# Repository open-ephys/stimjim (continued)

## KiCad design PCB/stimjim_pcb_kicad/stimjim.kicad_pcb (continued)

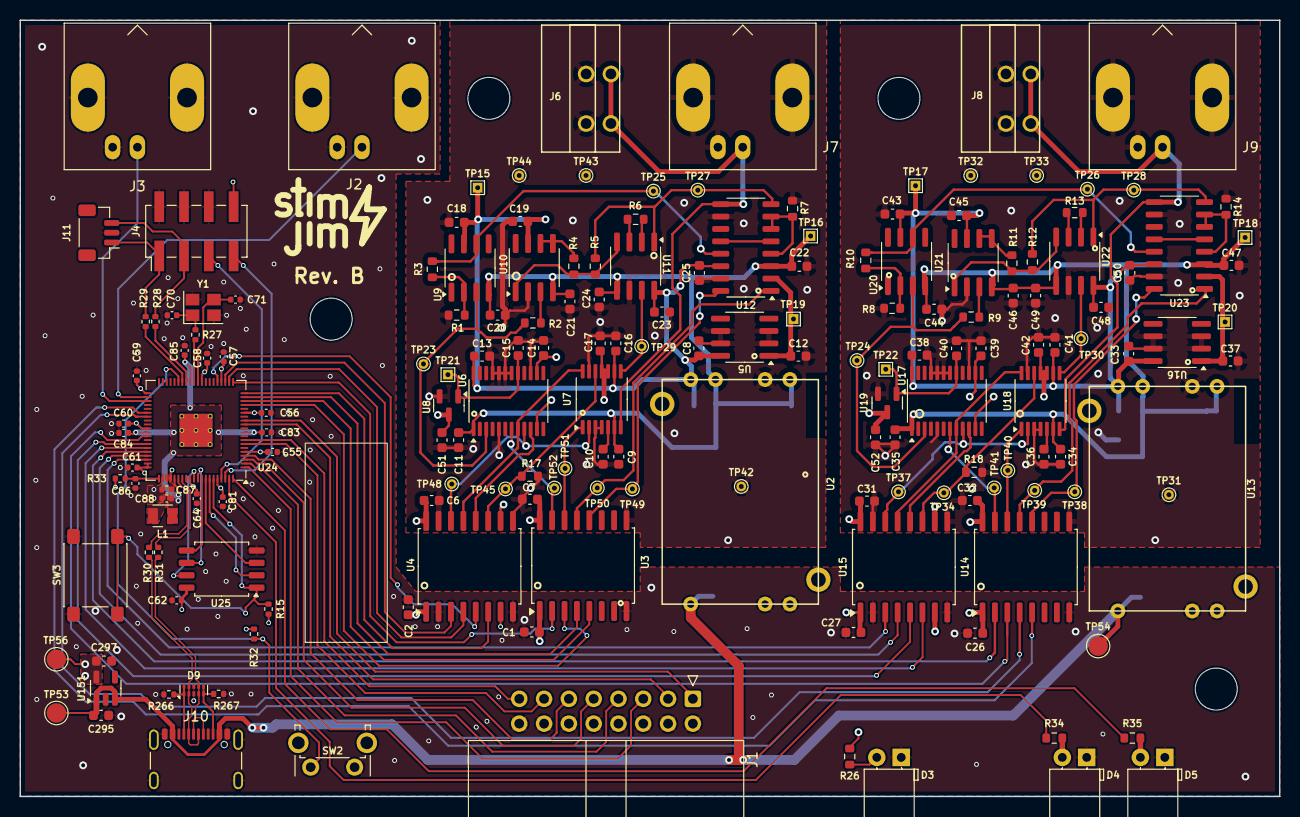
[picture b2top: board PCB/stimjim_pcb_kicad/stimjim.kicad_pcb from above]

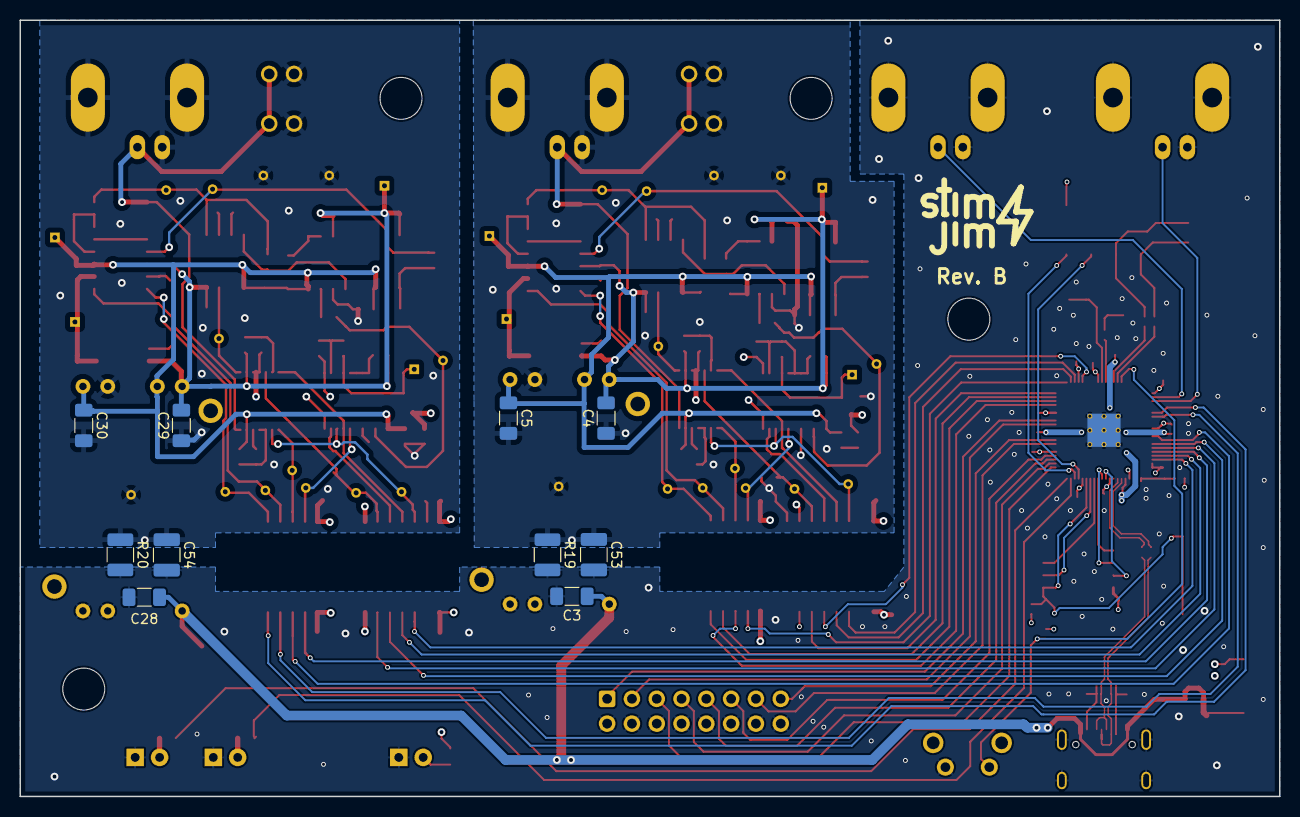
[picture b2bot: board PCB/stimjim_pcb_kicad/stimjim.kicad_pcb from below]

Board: 4 copper layers, 129.0 x 79.5 mm, 190 parts (10 on the bottom side), 113 nets.

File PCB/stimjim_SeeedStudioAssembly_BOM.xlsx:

Designator | MPN | Quantity | Link |  | Package | Designation | Unit cost | Total cost | Assembly notes
C26,C27,C31,C32,C34,C35,C38,C39,C42,C41,C2,C7,C6,C1,C13,C43,C44,C18,C20,C9,C14,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 | CL10F104ZO8NNNC | 36 | CL10F104ZO8NNNC |  | C_0603_1608Metric | 0.1uF | 0.038 | 1.368
C29,C28,C30,C4,C5,C3 | CC1206ZKY5V7BB106 | 6 | 311-1376-1-ND |  | C_1206_3216Metric_Pad1.42x1.75mm_HandSolder | 10uF | 0.4 | 2.4
C52,C51,C33,C37,C40,C8,C12,C15,C36,C10 | CL10B105KO8NNNC | 10 | 1276-1019-1-ND |  | C_0603_1608Metric | 1uF | 0.1 | 1
C53,C54 | C1206C222MGRAC7800 | 2 | 399-13198-1-ND |  | C_1210_3225Metric_Pad1.42x2.65mm_HandSolder | 2.2nF | 0.92 | 1.84
D2,D1 | 5300H5 | 2 | L20015-ND |  | LED_D5.0mm_Horizontal_O1.27mm_Z3.0mm | LED | 0.64 | 1.28
J1 | 302-R161 | 1 | ED10535-ND |  | Multicomp_MC9A22-1634_2x08_P2.54mm_Horizontal | Conn_02x08_Odd_Even | 0.48 | 0.48
J6,J8 | 1-2834016-2 | 2 | A123829-ND |  | 1-2834016-2 _TERM_BLK_2P_SIDE_ENT_2.54MM_PCB | Push_Terminal_01x02 | 1.12 | 2.24
J9,J3,J7,J2 | 731375003 | 4 | WM5514-ND |  | 731375003 | Conn_Coaxial | 1.48 | 5.92
R13,R6 | RR0816P-182-D | 2 | RR08P1.8KDCT-ND |  | R_0603_1608Metric | 1.8k | 0.11 | 0.22
R14,R7 | RR0816P-102-D | 2 | RR08P1.0KDCT-ND |  | R_0603_1608Metric | 1k | 0.11 | 0.22
R16,R15 | RR0816P-201-D | 2 | RR08P200DCT-ND |  | R_0603_1608Metric | 200 | 0.11 | 0.22
R17,R18,R1,R8 | ERA-3AEB103V | 4 | P10KDBCT-ND |  | R_0603_1608Metric | 10k | 0.35 | 1.4
R19,R20 | CHV1206-JW-105ELF | 2 | CHV1206-JW-105ELFCT-ND |  | R_1210_3225Metric_Pad1.42x2.65mm_HandSolder | 1M | 0.3 | 0.6
R2,R9,R11,R4 | ERA-3ARW302V | 4 | P3.0KBECT-ND |  | R_0603_1608Metric | 3k | 0.8 | 3.2
R3,R10 | ERA-3AEB4991V | 2 | P4.99KDBCT-ND |  | R_0603_1608Metric | 4.99k | 0.35 | 0.7
R5,R12 | RR0816P-101-D | 2 | RR08P100DCT-ND |  | R_0603_1608Metric | 100 | 0.1 | 0.2
SW1 | EVQ-PF303M | 1 | P12212S-ND |  | EVQ-PF303K | SW_Push | 0.23 | 0.23
U1 | DEV-14055 | 1 | 1568-1443-ND |  | Teensy35_36_noInternalPins | Teensy3.5 | 26.25 | 26.25 | After soldering male pins onto this part, it should be inserted into the female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
U1 | PPTC241LFBN-RC | 2 | S7022-ND |  | 24-pin female headers, 2.54mm pitch | Female headers | 1.37 | 2.74 | These should be soldered onto the topside of the board at location U1.
U1 | PREC024SAAN-RC | 2 | S1012EC-24-ND |  | 24-pin male headers, 2.54mm pitch | male pin headers | 0.46 | 0.92 | These should be soldered onto the bottom side of the Teensy (MPN DEV-14055)
U10,U21 | AMP03GSZ-RL | 2 | AMP03GSZ-RLCT-ND |  | SOIC-8_3.9x4.9mm_P1.27mm | AMP03 | 7.4 | 14.8
U14,U3 | ISO7760DWR | 2 | 296-48142-1-ND |  | SOIC-16W_7.5x10.3mm_P1.27mm | ISO7760 | 4.44 | 8.88
U15,U4 | ISO7741DWR | 2 | 296-47781-1-ND |  | SOIC-16W_7.5x10.3mm_P1.27mm | ISO7741 | 3.76 | 7.52
U17,U6 | AD5752AREZ | 2 | AD5752AREZ-ND |  | TSSOP-24_4.4x7.8mm_P0.65mm | AD5752 | 15.96 | 31.92
U18,U7 | AD7321BRUZ-REEL7 | 2 | AD7321BRUZ-REEL7CT-ND |  | TSSOP-14_4.4x5mm_P0.65mm | AD7321 | 7.84 | 15.68
U19,U8 | AD1582ARTZ-REEL7 | 2 | AD1582ARTZREEL7CT-ND |  | SOT-23 | AD1582 | 1.76 | 3.52
U2,U13 | CC3-0512DF-E | 2 | 445-2465-ND |  | CC3-0512DF-E | CC3-0512DF-E | 11.21 | 22.42
U20,U9 | OPA197IDR | 2 | 296-43866-1-ND |  | SOIC-8_3.9x4.9mm_P1.27mm | OPA197 | 1.6 | 3.2
U22,U11 | INA826AIDR | 2 | 296-30238-1-ND |  | SOIC-8_3.9x4.9mm_P1.27mm | INA826 | 2.81 | 5.62
U23,U12 | DG509BEY-T1-E3 | 2 | DG509BEY-T1-E3CT-ND |  | SOIC-16_3.9x9.9mm_P1.27mm | DG509ACWE | 2.43 | 4.86
U5,U16 | MC78L05ACDX | 2 | MC78L05ACDXCT-ND |  | SOIC-8_3.9x4.9mm_P1.27mm | L78L05_SO8 | 0.48 | 0.96

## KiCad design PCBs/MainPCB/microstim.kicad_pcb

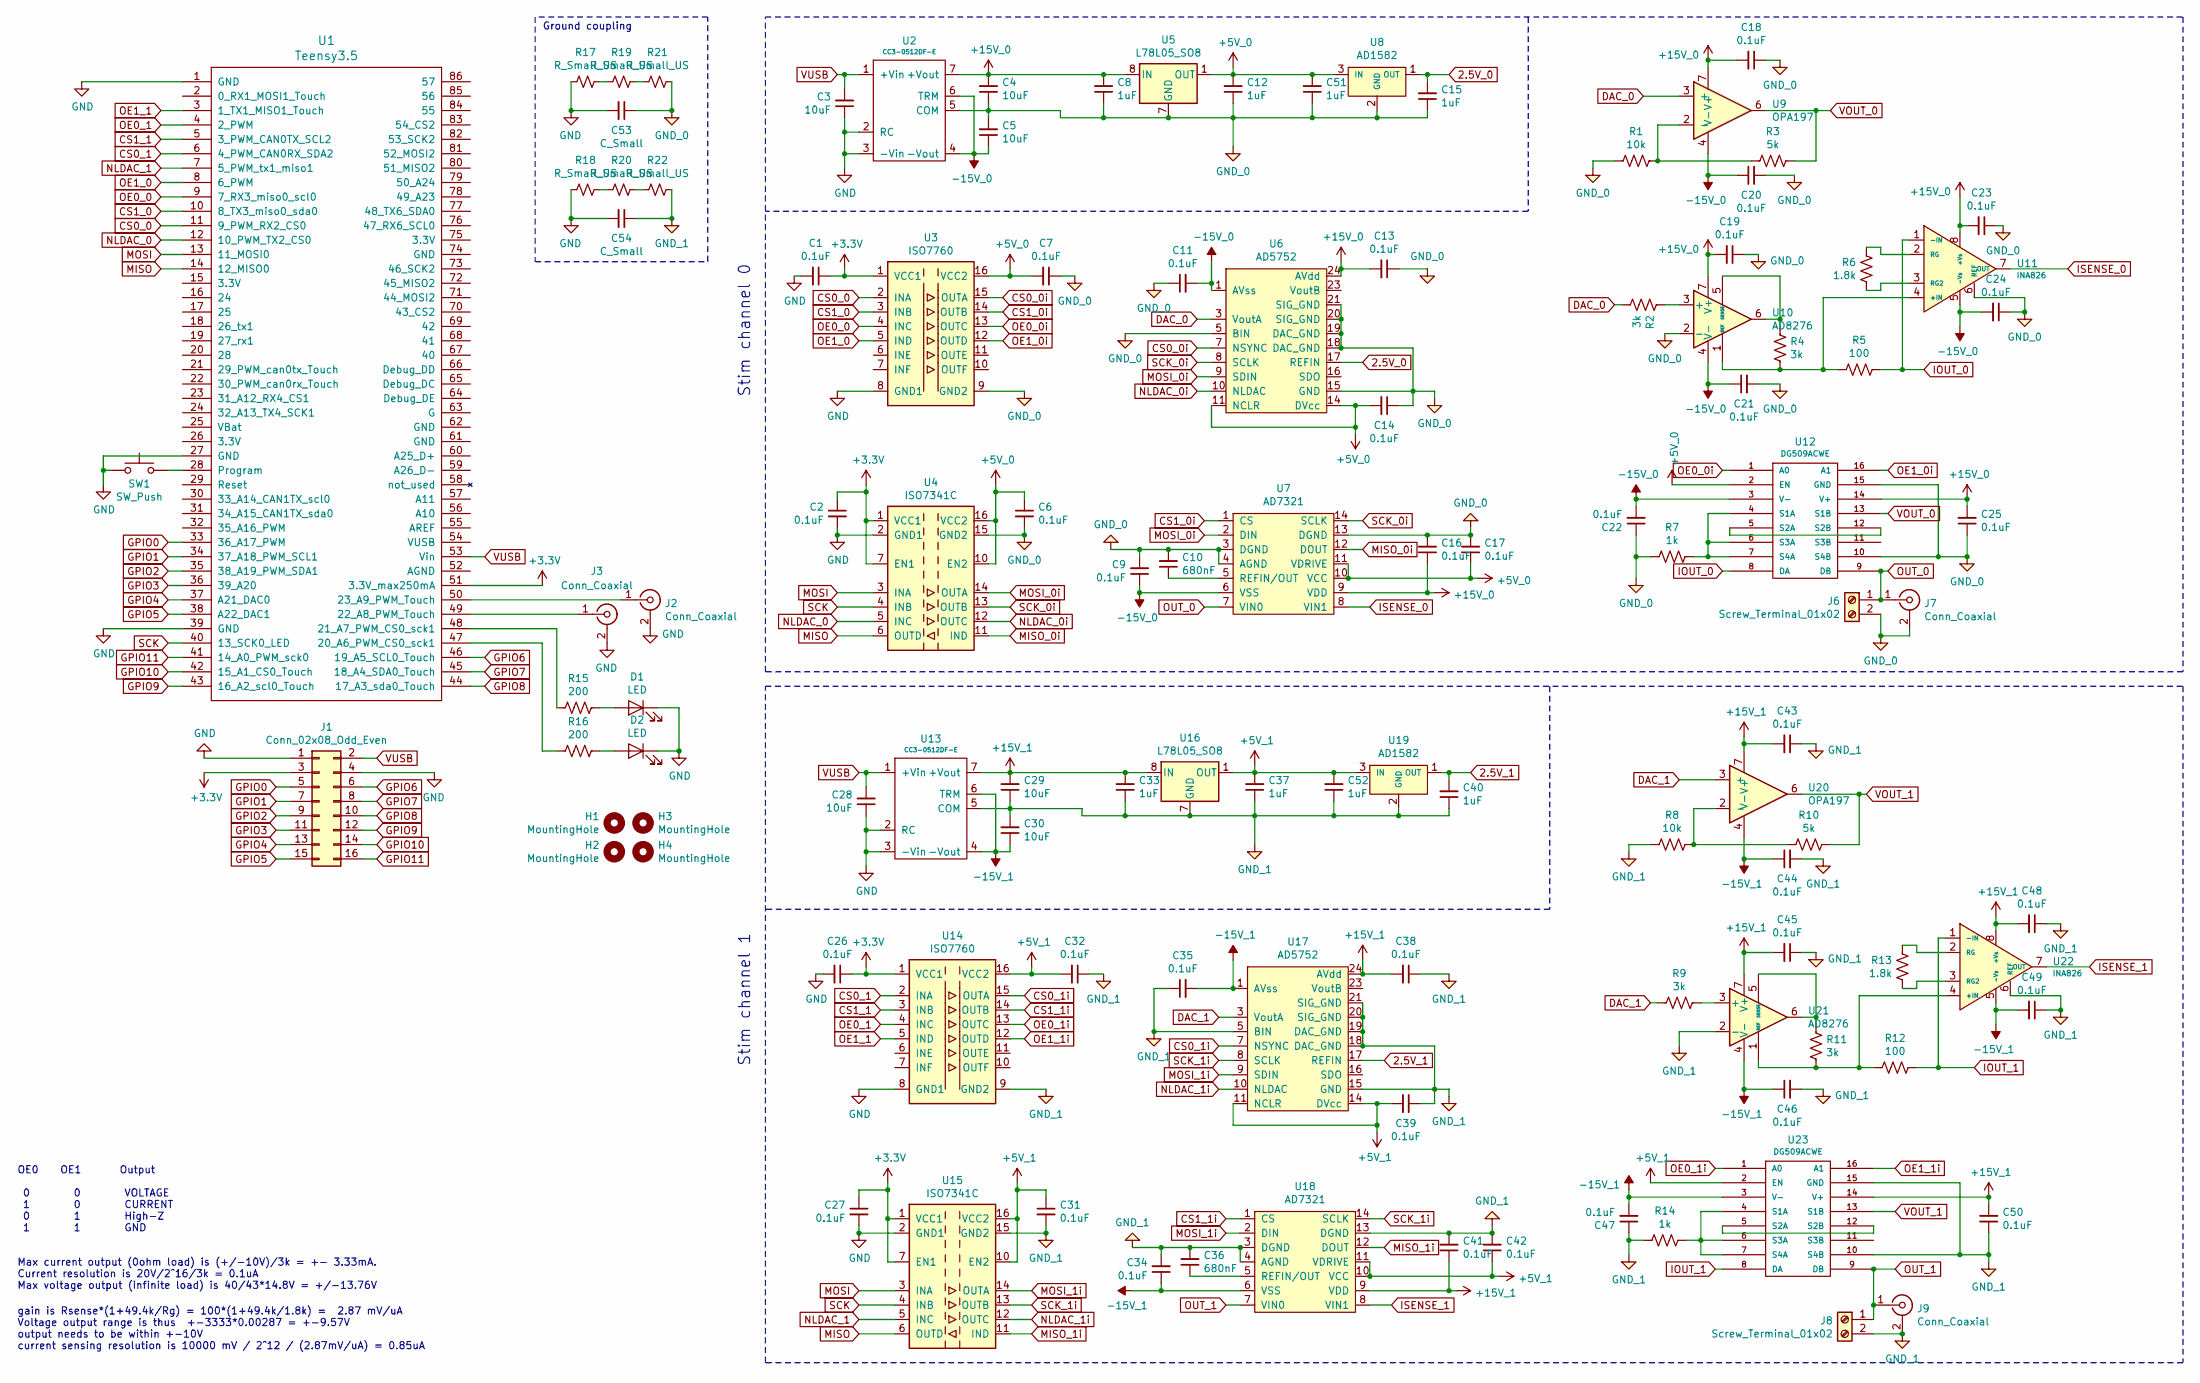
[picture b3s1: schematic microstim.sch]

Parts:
C1, C2, C6, C7, C9, C11, C13, C14, C16, C17, C18, C19, C20, C21, C22, C23, C24, C25, C26, C27, C31, C32, C34, C35, C38, C39, C41, C42, C43, C44, C45, C46, C47, C48, C49, C50: 0.1uF; C_0603_1608Metric
C3, C4, C5, C28, C29, C30: 10uF; C_1206_3216Metric_Pad1.42x1.75mm_HandSolder
C8, C12, C15, C33, C37, C40, C51, C52: 1uF; C_0603_1608Metric
C10, C36: 680nF; C_0603_1608Metric
C53, C54: C_Small; C_Disc_D12.5mm_W5.0mm_P10.00mm
D1, D2: LED; LED_D5.0mm_Horizontal_O1.27mm_Z3.0mm_pinSwapped
H1, H2, H3, H4: MountingHole; MountingHole_4.3mm_M4
J1: Conn_02x08_Odd_Even; Multicomp_MC9A22-1634_2x08_P2.54mm_Horizontal
J2, J3, J7, J9: Conn_Coaxial; 731375003
J6, J8: Screw_Terminal_01x02; 1-2834016-2 _TERM_BLK_2P_SIDE_ENT_2.54MM_PCB
R1, R8: 10k; R_0603_1608Metric
R2, R4, R9, R11: 3k; R_0603_1608Metric
R3, R10: 5k; R_0603_1608Metric
R5, R12: 100; R_0603_1608Metric
R6, R13: 1.8k; R_0603_1608Metric
R7, R14: 1k; R_0603_1608Metric
R15, R16: 200; R_0603_1608Metric
R17, R18, R19, R20, R21, R22: R_Small_US; R_1210_3225Metric_Pad1.42x2.65mm_HandSolder
SW1: SW_Push; EVQ-PF303K
U1: Teensy3.5; Teensy35_36_noInternalPins
U2, U13: CC3-0512DF-E
U3, U14: ISO7760; SOIC-16W_7.5x10.3mm_P1.27mm
U4, U15: ISO7341C; SOIC-16W_7.5x10.3mm_P1.27mm
U5, U16: L78L05_SO8; SOIC-8_3.9x4.9mm_P1.27mm
U6, U17: AD5752; TSSOP-24_4.4x7.8mm_P0.65mm
U7, U18: AD7321; TSSOP-14_4.4x5mm_P0.65mm
U8, U19: AD1582; SOT-23
U9, U20: OPA197; SOIC-8_3.9x4.9mm_P1.27mm
U10, U21: AD8276; SOIC-8_3.9x4.9mm_P1.27mm
U11, U22: INA826; SOIC-8_3.9x4.9mm_P1.27mm
U12, U23: DG509ACWE; SOIC-16_3.9x9.9mm_P1.27mm

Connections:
2.5V_0: C15.2, U6.17 (REFIN), U8.1 (OUT)
2.5V_1: C40.2, U17.17 (REFIN), U19.1 (OUT)
+3V3: C1.1, C2.1, C26.1, C27.1, J1.3, U1.51 (3.3V_max250mA), U3.1 (VCC1), U4.1 (VCC1), U4.7 (EN1), U14.1 (VCC1), U15.1 (VCC1), U15.7 (EN1)
+5V_0: C6.1, C7.2, C12.2, C14.2, C17.1, C51.2, U3.16 (VCC2), U4.10 (EN2), U4.16 (VCC2), U5.1 (OUT), U6.11 (NCLR), U6.14 (DVcc), U7.10 (VCC), U7.11 (VDRIVE), U8.3 (IN), U12.2 (EN)
+5V_1: C31.1, C32.2, C37.2, C39.2, C42.1, C52.2, U14.16 (VCC2), U15.10 (EN2), U15.16 (VCC2), U16.1 (OUT), U17.11 (NCLR), U17.14 (DVcc), U18.10 (VCC), U18.11 (VDRIVE), U19.3 (IN), U23.2 (EN)
+15V_0: C4.2, C8.2, C13.2, C16.1, C18.2, C19.2, C23.2, C25.2, U2.7 (+Vout), U5.8 (IN), U6.24 (AVdd), U7.9 (VDD), U9.7 (V+), U10.7 (V+), U11.8 (+Vs), U12.14 (V+)
+15V_1: C29.2, C33.2, C38.2, C41.1, C43.2, C45.2, C48.2, C50.2, U13.7 (+Vout), U16.8 (IN), U17.24 (AVdd), U18.9 (VDD), U20.7 (V+), U21.7 (V+), U22.8 (+Vs), U23.14 (V+)
-15V_0: C5.1, C9.1, C11.2, C20.1, C21.1, C22.2, C24.2, U2.4 (-Vout), U2.6 (TRM), U6.1 (AVss), U7.6 (VSS), U9.4 (V-), U10.4 (V-), U11.5 (-Vs), U12.3 (V-)
-15V_1: C30.1, C34.1, C35.2, C44.1, C46.1, C47.2, C49.2, U13.4 (-Vout), U13.6 (TRM), U17.1 (AVss), U18.6 (VSS), U20.4 (V-), U21.4 (V-), U22.5 (-Vs), U23.3 (V-)
CS0_0: U1.11 (9_PWM_RX2_CS0), U3.2 (INA)
CS0_0i: U3.15 (OUTA), U6.7 (NSYNC)
CS0_1: U1.6 (4_PWM_CAN0RX_SDA2), U14.2 (INA)
CS0_1i: U14.15 (OUTA), U17.7 (NSYNC)
CS1_0: U1.10 (8_TX3_miso0_sda0), U3.3 (INB)
CS1_0i: U3.14 (OUTB), U7.1 (CS)
CS1_1: U1.5 (3_PWM_CAN0TX_SCL2), U14.3 (INB)
CS1_1i: U14.14 (OUTB), U18.1 (CS)
DAC_0: R2.2, U6.3 (VoutA), U9.3 (+)
DAC_1: R9.2, U17.3 (VoutA), U20.3 (+)
GND: C1.2, C2.2, C3.1, C26.2, C27.2, C28.1, C53.2, C54.2, D1.1 (K), D2.1 (K), J1.1, J1.4, J2.2 (Ext), J3.2 (Ext), R17.2, R18.2, SW1.1, U1.1 (GND), U1.27 (GND), U1.39 (GND), U2.2 (RC), U2.3 (-Vin), U3.8 (GND1), U4.2 (GND1), U4.8 (GND1), U13.2 (RC), U13.3 (-Vin), U14.8 (GND1), U15.2 (GND1), U15.8 (GND1)
GND_0: C4.1, C5.2, C6.2, C7.1, C8.1, C9.2, C10.2, C11.1, C12.1, C13.1, C14.1, C15.1, C16.2, C17.2, C18.1, C19.1, C20.2, C21.2, C22.1, C23.1, C24.1, C25.1, C51.1, C53.1, J6.2, J7.2 (Ext), R1.1, R7.2, R21.1, U2.5 (COM), U3.9 (GND2), U4.9 (GND2), U4.15 (GND2), U5.2 (GND), U5.3 (GND), U5.6 (GND), U5.7 (GND), U6.5 (BIN), U6.15 (GND), U6.18 (DAC_GND), U6.19 (DAC_GND), U6.20 (SIG_GND), U6.21 (SIG_GND), U7.3 (DGND), U7.4 (AGND), U7.13 (DGND), U8.2 (GND), U10.2 (-), U11.6 (REF), U12.10 (S4B), U12.15 (GND)
GND_1: C29.1, C30.2, C31.2, C32.1, C33.1, C34.2, C35.1, C36.2, C37.1, C38.1, C39.1, C40.1, C41.2, C42.2, C43.1, C44.2, C45.1, C46.2, C47.1, C48.1, C49.1, C50.1, C52.1, C54.1, J8.2, J9.2 (Ext), R8.1, R14.1, R22.1, U13.5 (COM), U14.9 (GND2), U15.9 (GND2), U15.15 (GND2), U16.2 (GND), U16.3 (GND), U16.6 (GND), U16.7 (GND), U17.5 (BIN), U17.15 (GND), U17.18 (DAC_GND), U17.19 (DAC_GND), U17.20 (SIG_GND), U17.21 (SIG_GND), U18.3 (DGND), U18.4 (AGND), U18.13 (DGND), U19.2 (GND), U21.2 (-), U22.6 (REF), U23.10 (S4B), U23.15 (GND)
GPIO0: J1.5, U1.33 (36_A17_PWM)
GPIO1: J1.7, U1.34 (37_A18_PWM_SCL1)
GPIO2: J1.9, U1.35 (38_A19_PWM_SDA1)
GPIO3: J1.11, U1.36 (39_A20)
GPIO4: J1.13, U1.37 (A21_DAC0)
GPIO5: J1.15, U1.38 (A22_DAC1)
GPIO6: J1.6, U1.46 (19_A5_SCL0_Touch)
GPIO7: J1.8, U1.45 (18_A4_SDA0_Touch)
GPIO8: J1.10, U1.44 (17_A3_sda0_Touch)
GPIO9: J1.12, U1.43 (16_A2_scl0_Touch)
GPIO10: J1.14, U1.42 (15_A1_CS0_Touch)
GPIO11: J1.16, U1.41 (14_A0_PWM_sck0)
IOUT_0: R5.2, U11.1 (-IN), U12.8 (DA)
IOUT_1: R12.2, U22.1 (-IN), U23.8 (DA)
ISENSE_0: U7.8 (VIN1), U11.7 (OUT)
ISENSE_1: U18.8 (VIN1), U22.7 (OUT)
MISO: U1.14 (12_MISO0), U4.6 (OUTD), U15.6 (OUTD)
MISO_0i: U4.11 (IND), U7.12 (DOUT)
MISO_1i: U15.11 (IND), U18.12 (DOUT)
MOSI: U1.13 (11_MOSI0), U4.3 (INA), U15.3 (INA)
MOSI_0i: U4.14 (OUTA), U6.9 (SDIN), U7.2 (DIN)
MOSI_1i: U15.14 (OUTA), U17.9 (SDIN), U18.2 (DIN)
NLDAC_0: U1.12 (10_PWM_TX2_CS0), U4.5 (INC)
NLDAC_0i: U4.12 (OUTC), U6.10 (NLDAC)
NLDAC_1: U1.7 (5_PWM_tx1_miso1), U15.5 (INC)
NLDAC_1i: U15.12 (OUTC), U17.10 (NLDAC)
unnamed: C10.1, U7.5 (REFIN/OUT)
unnamed: C36.1, U18.5 (REFIN/OUT)
unnamed: D1.2 (A), R15.1
unnamed: D2.2 (A), R16.1
unnamed: J2.1 (In), U1.50 (23_A9_PWM_Touch)
unnamed: J3.1 (In), U1.49 (22_A8_PWM_Touch)
unnamed: R1.2, R3.1, U9.2 (-)
unnamed: R2.1, U10.3 (+)
unnamed: R4.1, R5.1, U10.1 (REF), U11.4 (+IN)
unnamed: R4.2, U10.5 (SENSE), U10.6
unnamed: R6.1, U11.3 (RG2)
unnamed: R6.2, U11.2 (RG)
unnamed: R7.1, U12.4 (S1A), U12.6 (S3A), U12.7 (S4A)
unnamed: R9.1, U21.3 (+)
unnamed: R8.2, R10.1, U20.2 (-)
unnamed: R11.1, R12.1, U21.1 (REF), U22.4 (+IN)
unnamed: R11.2, U21.5 (SENSE), U21.6
unnamed: R13.1, U22.3 (RG2)
unnamed: R13.2, U22.2 (RG)
unnamed: R14.2, U23.4 (S1A), U23.6 (S3A), U23.7 (S4A)
unnamed: R15.2, U1.48 (21_A7_PWM_CS0_sck1)
unnamed: R16.2, U1.47 (20_A6_PWM_CS0_sck1)
unnamed: R17.1, R19.2
unnamed: R18.1, R20.2
unnamed: R19.1, R21.2
unnamed: R20.1, R22.2
unnamed: SW1.2, U1.28 (Program)
unnamed: U12.5 (S2A), U12.12 (S2B)
unnamed: U23.5 (S2A), U23.12 (S2B)
OE0_0: U1.9 (7_RX3_miso0_scl0), U3.4 (INC)
OE0_0i: U3.13 (OUTC), U12.1 (A0)
OE0_1: U1.4 (2_PWM), U14.4 (INC)
OE0_1i: U14.13 (OUTC), U23.1 (A0)
OE1_0: U1.8 (6_PWM), U3.5 (IND)
OE1_0i: U3.12 (OUTD), U12.16 (A1)
OE1_1: U1.3 (1_TX1_MISO1_Touch), U14.5 (IND)
OE1_1i: U14.12 (OUTD), U23.16 (A1)
OUT_0: J6.1, J7.1 (In), U7.7 (VIN0), U12.9 (DB)
OUT_1: J8.1, J9.1 (In), U18.7 (VIN0), U23.9 (DB)
SCK: U1.40 (13_SCK0_LED), U4.4 (INB), U15.4 (INB)
SCK_0i: U4.13 (OUTB), U6.8 (SCLK), U7.14 (SCLK)
SCK_1i: U15.13 (OUTB), U17.8 (SCLK), U18.14 (SCLK)
VOUT_0: R3.2, U9.6, U12.13 (S1B)
VOUT_1: R10.2, U20.6, U23.13 (S1B)
VUSB: C3.2, C28.2, J1.2, U1.53 (Vin), U2.1 (+Vin), U13.1 (+Vin)

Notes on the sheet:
gain is Rsense*(1+49.4k/Rg) = 100*(1+49.4k/1.8k) = 2.87 mV/uA Voltage output range is thus +-3333*0.00287 = +-9.57V output needs to be within +-10V current sensing resolution is 10000 mV / 2^12 / (2.87mV/uA) = 0.85uA
Max current output (0ohm load) is (+/-10V)/3k = +- 3.33mA. Current resolution is 20V/2^16/3k = 0.1uA Max voltage output (infinite load) is 40/43*14.8V = +/-13.76V
OE0 OE1 Output 0 0 VOLTAGE 1 0 CURRENT 0 1 High-Z 1 1 GND
Stim channel 1
Stim channel 0
Ground coupling

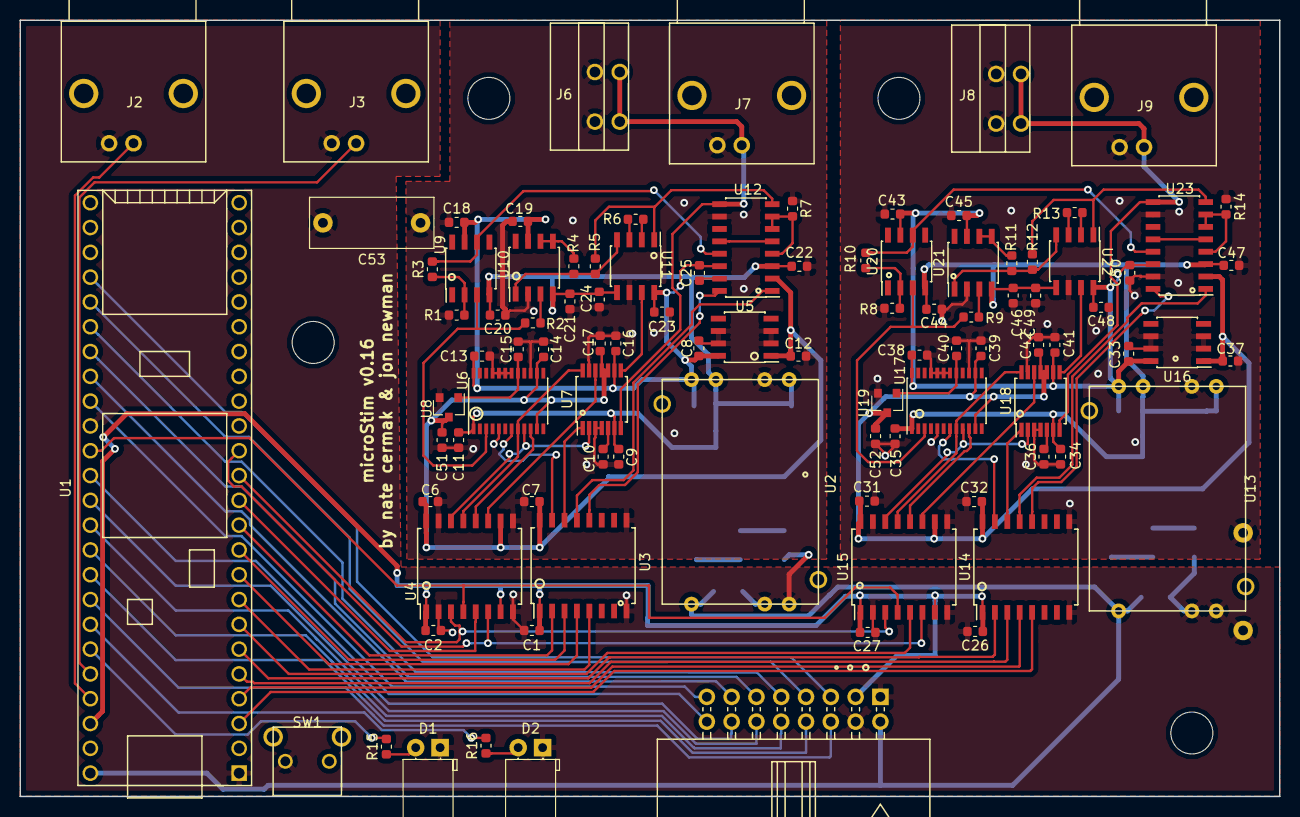
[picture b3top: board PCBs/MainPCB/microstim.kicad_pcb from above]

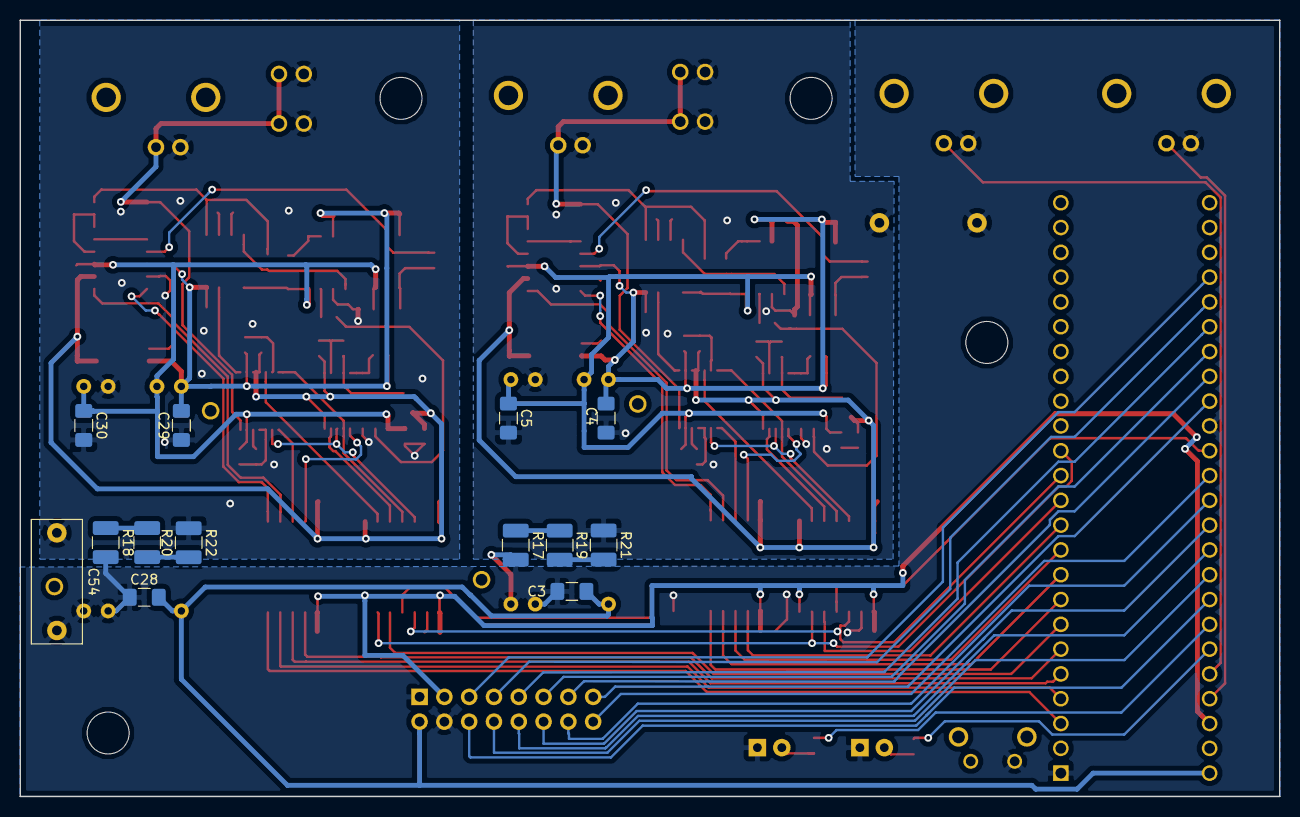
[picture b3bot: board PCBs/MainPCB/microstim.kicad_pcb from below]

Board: 2 copper layers, 129.0 x 79.5 mm, 113 parts (13 on the bottom side), 92 nets.

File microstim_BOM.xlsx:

Id | Designator | Package | Quantity | Designation | MPN | Digikey part # | Unit cost | Total cost | Notes
1 | SW1 | EVQ-PF303K | 1 | SW_Push | EVQ-PF303M | P12212S-ND | 0.23 | 0.23
2 | R2,R9,R11,R4 | R_0603_1608Metric | 4 | 3k | ERA-3ARW302V | P3.0KBECT-ND | 0.8 | 3.2
3 | U2,U13 | CC3-0512DF-E | 2 | CC3-0512DF-E | CC3-0512DF-E | 445-2465-ND | 11.21 | 22.42
4 | C52,C51,C33,C37,C40,C8,C12,C15 | C_0603_1608Metric | 8 | 1uF | CL10B105KO8NNNC | 1276-1019-1-ND | 0.1 | 0.8
5 | U5,U16 | SOIC-8_3.9x4.9mm_P1.27mm | 2 | L78L05_SO8 | MC78L05ACDX | MC78L05ACDXCT-ND | 0.48 | 0.96
6 | J6,J8 | 1-2834016-2 _TERM_BLK_2P_SIDE_ENT_2.54MM_PCB | 2 | Screw_Terminal_01x02 | 1-2834016-2 | A123829-ND | 1.02 | 2.04
7 | C26,C27,C31,C32,C34,C35,C38,C39,C42,C41,C2,C7,C6,C1,C13,C43,C44,C18,C20,C9,C14,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 | C_0603_1608Metric | 36 | 0.1uF | CL10F104ZO8NNNC | CL10F104ZO8NNNC | 0.038 | 1.368
8 | C36,C10 | C_0603_1608Metric | 2 | 680nF | 885012206070 | 732-7988-1-ND | 0.1 | 0.2
9 | C29,C28,C30,C4,C5,C3 | C_1206_3216Metric_Pad1.42x1.75mm_HandSolder | 6 | 10uF | CC1206ZKY5V7BB106 | 311-1376-1-ND | 0.4 | 2.4
10 | U14,U3 | SOIC-16W_7.5x10.3mm_P1.27mm | 2 | ISO7760 | ISO7760DWR | 296-48142-1-ND | 4.44 | 8.88
11 | U15,U4 | SOIC-16W_7.5x10.3mm_P1.27mm | 2 | ISO7341C | ISO7341FCDWR | 296-47779-1-ND | 4.32 | 8.64
12 | U18,U7 | TSSOP-14_4.4x5mm_P0.65mm | 2 | AD7321 | AD7321BRUZ-REEL7 | AD7321BRUZ-REEL7CT-ND | 7.84 | 15.68
13 | U17,U6 | TSSOP-24_4.4x7.8mm_P0.65mm | 2 | AD5752 | AD5752AREZ | AD5752AREZ-ND | 15.96 | 31.92 | Alternate part: AD5752RBREZ-ND
14 | U19,U8 | SOT-23 | 2 | AD1582 | AD1582ARTZ-REEL7 | AD1582ARTZREEL7CT-ND | 1.76 | 3.52
15 | U20,U9 | SOIC-8_3.9x4.9mm_P1.27mm | 2 | OPA197 | OPA197IDR | 296-43866-1-ND | 1.6 | 3.2
16 | D2,D1 | LED_D5.0mm_Horizontal_O1.27mm_Z3.0mm | 2 | LED | 5300H5 | L20015-ND | 0.64 | 1.28
17 | J1 | Multicomp_MC9A22-1634_2x08_P2.54mm_Horizontal | 1 | Conn_02x08_Odd_Even | 302-R161 | ED10535-ND | 0.48 | 0.48
18 | U1 | Teensy35_36_noInternalPins | 1 | Teensy3.5 | DEV-14055 | 1568-1443-ND | 26.25 | 26.25
19 | J9,J3,J7,J2 | 731375003 | 4 | Conn_Coaxial | 731375003 | WM5514-ND | 1.48 | 5.92
20 | R14,R7 | R_0603_1608Metric | 4 | 1k | RR0816P-102-D | RR08P1.0KDCT-ND | 0.11 | 0.44
 | R1,R8 | R_0603_1608Metric | 2 | 10k
21 | R3,R10 | R_0603_1608Metric | 2 | 5k
 | R21,R17,R19,R20,R22,R18 | R_1210_3225Metric_Pad1.42x2.65mm_HandSolder | 6 | R_Small_US |  | 541-2312-1-ND | 1.41
 | C53,C54 | C_Disc_D12.5mm_W5.0mm_P10.00mm | 2 | C_Small |  | 399-9520-1-ND | 0.78
22 | R13,R6 | R_0603_1608Metric | 2 | 1.8k | RR0816P-182-D | RR08P1.8KDCT-ND | 0.11 | 0.22
23 | R5,R12 | R_0603_1608Metric | 2 | 100 | RR0816P-101-D | RR08P100DCT-ND | 0.1 | 0.2
24 | U10,U21 | SOIC-8_3.9x4.9mm_P1.27mm | 2 | AD8276 | AD8276ARZ | AD8276ARZ-ND | 2.73 | 5.46
25 | U22,U11 | SOIC-8_3.9x4.9mm_P1.27mm | 2 | INA826 | INA826AIDR | 296-30238-1-ND | 2.81 | 5.62
26 | U23,U12 | SOIC-16_3.9x9.9mm_P1.27mm | 2 | DG509ACWE | DG509BEY-T1-E3 | DG509BEY-T1-E3CT-ND | 2.43 | 4.86 | Alternate part: DG409DY-T1-E3CT-ND
27 | R16,R15 | R_0603_1608Metric | 4 | 200 | RR0816P-201-D | RR08P200DCT-ND | 0.11 | 0.44
28 | U1 | 24-pin female headers, 2.54mm pitch | 2 | Female headers | SSQ-124-03-T-S | SAM1206-24-ND | 2.67 | 5.34
29 | U1 | 24-pin male headers, 2.54mm pitch | 2 | male pin headers | PREC024SAAN-RC | S1012EC-24-ND | 0.46 | 0.92
 | Enclosure |  | 1 | BOX ALUM CLR/SLV 3.5"L X 5.77"W | EXN-23359-SVP | 377-2550-ND | 24.5 | 24.5
 | Combined PCB |  | 1 |  |  | Seeedstudio | 6.298 | 6.298 | At quantity 10, total cost is 62.98
 |  |  |  |  |  |  |  | 193.686

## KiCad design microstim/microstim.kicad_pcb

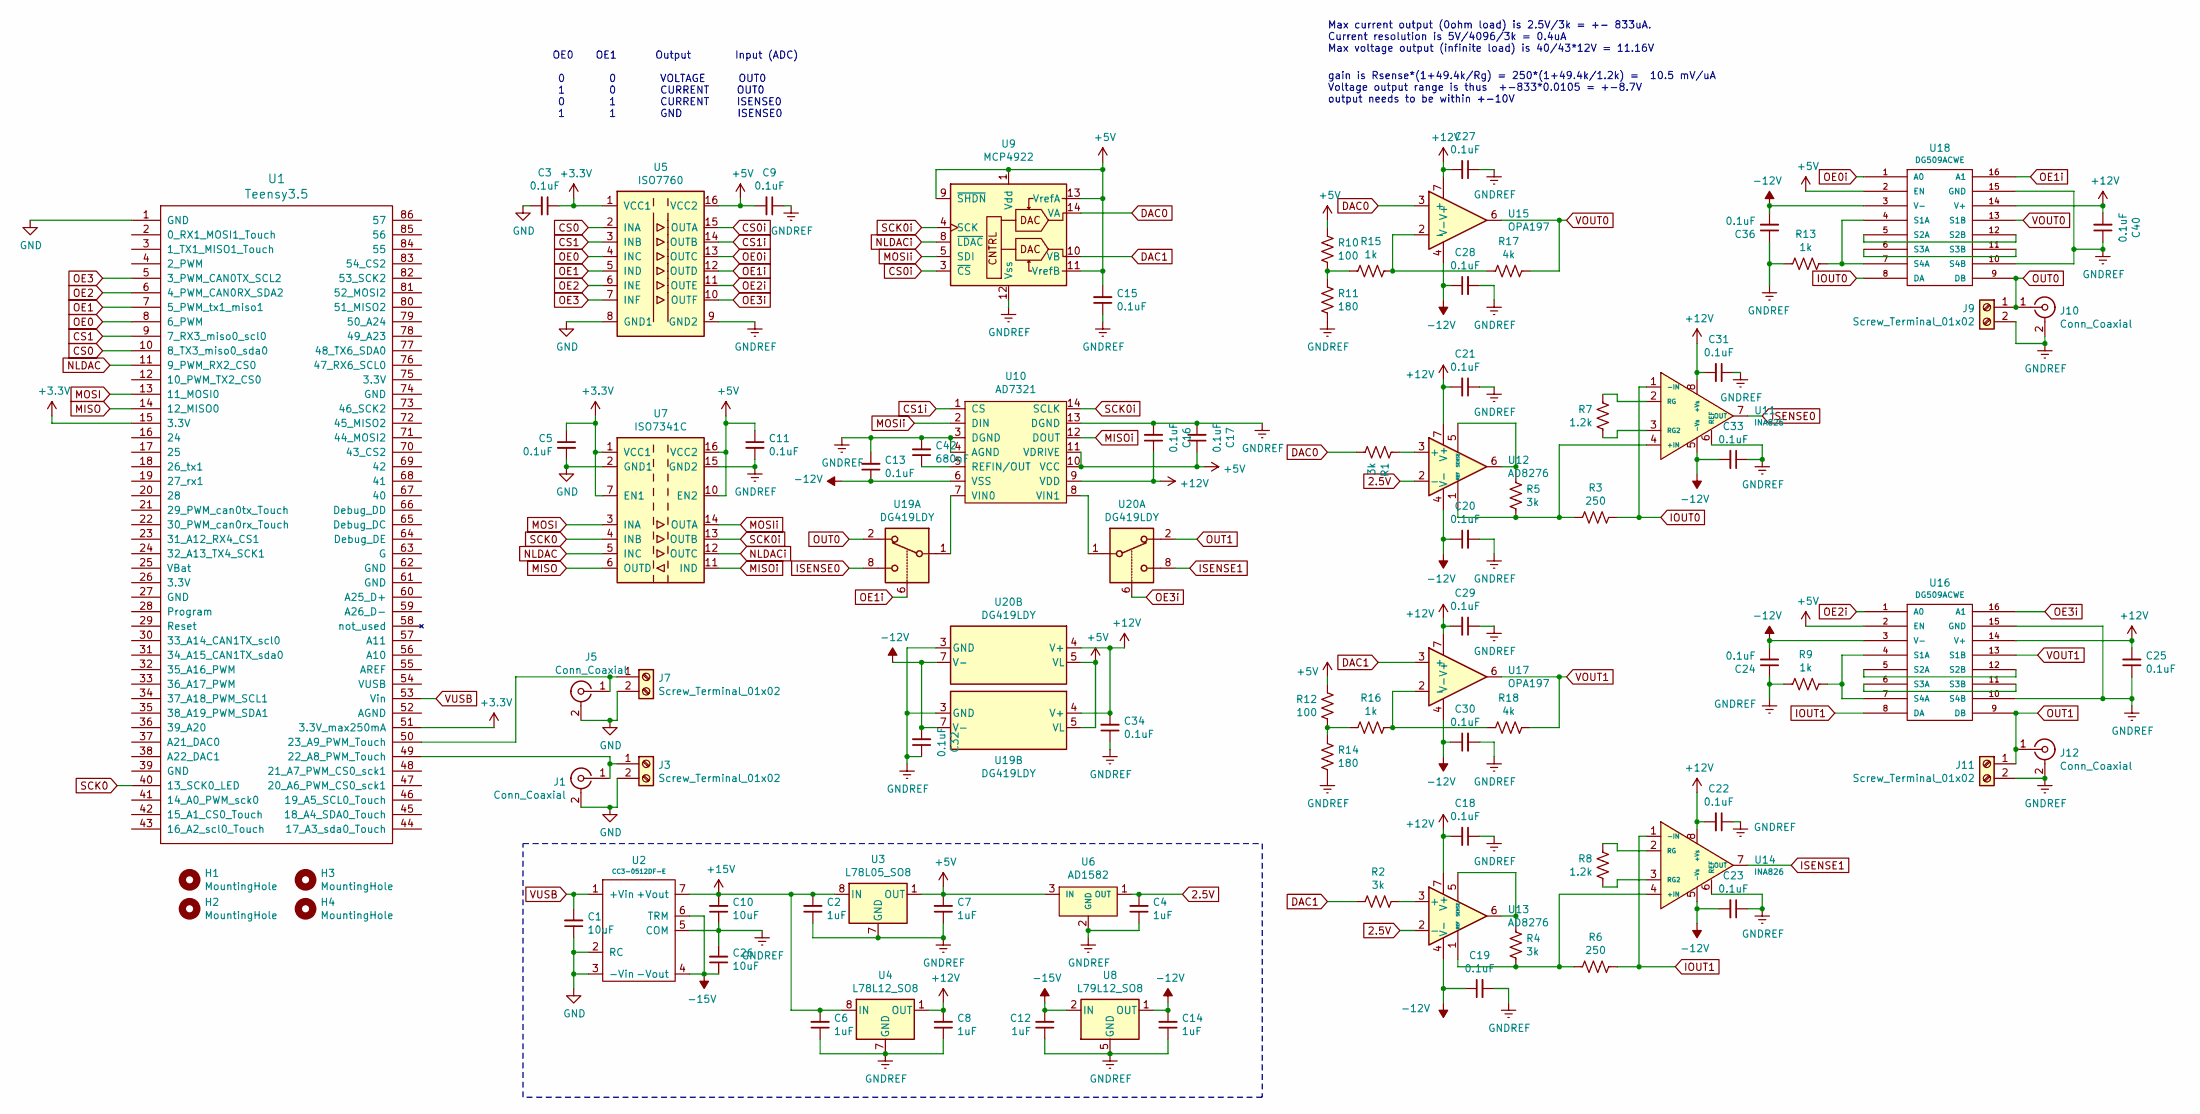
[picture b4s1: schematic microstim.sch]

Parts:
C1, C10, C26: 10uF; C_1206_3216Metric_Pad1.42x1.75mm_HandSolder
C2, C4, C6, C7, C8, C12, C14: 1uF; C_0603_1608Metric
C3, C5, C9, C11, C13, C15, C16, C17, C18, C19, C20, C21, C22, C23, C24, C25, C27, C28, C29, C30, C31, C32, C33, C34, C36, C40: 0.1uF; C_0603_1608Metric
C42: 680nF; C_0603_1608Metric
H1, H2, H3, H4: MountingHole; MountingHole_4.3mm_M4
J1, J5, J10, J12: Conn_Coaxial; 731375003
J3, J7, J9, J11: Screw_Terminal_01x02; 1-2834016-2 _TERM_BLK_2P_SIDE_ENT_2.54MM_PCB
R1, R2, R4, R5: 3k; R_0603_1608Metric
R3, R6: 250; R_0603_1608Metric
R7, R8: 1.2k; R_0603_1608Metric
R9, R13, R15, R16: 1k; R_0603_1608Metric
R10, R12: 100; R_0603_1608Metric
R11, R14: 180; R_0603_1608Metric
R17, R18: 4k; R_0603_1608Metric
U1: Teensy3.5; Teensy35_36_noInternalPins
U2: CC3-0512DF-E
U3: L78L05_SO8; SOIC-8_3.9x4.9mm_P1.27mm
U4: L78L12_SO8; SOIC-8_3.9x4.9mm_P1.27mm
U5: ISO7760; SOIC-16W_7.5x10.3mm_P1.27mm
U6: AD1582; SOT-23
U7: ISO7341C; SOIC-16W_7.5x10.3mm_P1.27mm
U8: L79L12_SO8; SOIC-8_3.9x4.9mm_P1.27mm
U9: MCP4922; SOIC-14_3.9x8.7mm_P1.27mm
U10: AD7321; TSSOP-14_4.4x5mm_P0.65mm
U11, U14: INA826; SOIC-8_3.9x4.9mm_P1.27mm
U12, U13: AD8276; SOIC-8_3.9x4.9mm_P1.27mm
U15, U17: OPA197; SOIC-8_3.9x4.9mm_P1.27mm
U16, U18: DG509ACWE; SOIC-16_3.9x9.9mm_P1.27mm
U19, U20: DG419LDY; SOIC-8_3.9x4.9mm_P1.27mm

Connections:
2.5V: C4.2, U6.1 (OUT), U12.2 (-), U13.2 (-)
+3V3: C3.1, C5.1, U1.15 (3.3V), U1.51 (3.3V_max250mA), U5.1 (VCC1), U7.1 (VCC1), U7.7 (EN1)
+5V: C7.2, C9.2, C11.1, C15.2, C17.1, R10.2, R12.2, U3.1 (OUT), U5.16 (VCC2), U6.3 (IN), U7.10 (EN2), U7.16 (VCC2), U9.1 (Vdd), U9.9 (~SHDN), U9.11 (VrefB), U9.13 (VrefA), U10.10 (VCC), U10.11 (VDRIVE), U16.2 (EN), U18.2 (EN), U19.5 (VL), U20.5 (VL)
+12V: C8.2, C16.1, C18.2, C21.2, C22.2, C25.2, C27.2, C29.2, C31.2, C34.2, C40.2, U4.1 (OUT), U10.9 (VDD), U11.8 (+Vs), U12.7 (V+), U13.7 (V+), U14.8 (+Vs), U15.7 (V+), U16.14 (V+), U17.7 (V+), U18.14 (V+), U19.4 (V+), U20.4 (V+)
+15V: C2.2, C6.2, C10.2, U2.7 (+Vout), U3.8 (IN), U4.8 (IN)
-12V: C13.1, C14.2, C19.1, C20.1, C23.2, C24.2, C28.1, C30.1, C32.2, C33.2, C36.2, U8.1 (OUT), U10.6 (VSS), U11.5 (-Vs), U12.4 (V-), U13.4 (V-), U14.5 (-Vs), U15.4 (V-), U16.3 (V-), U17.4 (V-), U18.3 (V-), U19.7 (V-), U20.7 (V-)
-15V: C12.2, C26.1, U2.4 (-Vout), U2.6 (TRM), U8.2 (IN), U8.3 (IN), U8.6 (IN), U8.7 (IN)
CS0: U1.10 (8_TX3_miso0_sda0), U5.2 (INA)
CS0i: U5.15 (OUTA), U9.3 (~CS)
CS1: U1.9 (7_RX3_miso0_scl0), U5.3 (INB)
CS1i: U5.14 (OUTB), U10.1 (CS)
DAC0: R1.2, U9.14 (VA), U15.3 (+)
DAC1: R2.2, U9.10 (VB), U17.3 (+)
GND: C1.1, C3.2, C5.2, J1.2 (Ext), J3.2, J5.2 (Ext), J7.2, U1.1 (GND), U2.2 (RC), U2.3 (-Vin), U5.8 (GND1), U7.2 (GND1), U7.8 (GND1)
GNDREF: C2.1, C4.1, C6.1, C7.1, C8.1, C9.1, C10.1, C11.2, C12.1, C13.2, C14.1, C15.1, C16.2, C17.2, C18.1, C19.2, C20.2, C21.1, C22.1, C23.1, C24.1, C25.1, C26.2, C27.1, C28.2, C29.1, C30.2, C31.1, C32.1, C33.1, C34.1, C36.1, C40.1, C42.2, J9.2, J10.2 (Ext), J11.2, J12.2 (Ext), R9.1, R11.1, R13.2, R14.1, U2.5 (COM), U3.2 (GND), U3.3 (GND), U3.6 (GND), U3.7 (GND), U4.2 (GND), U4.3 (GND), U4.6 (GND), U4.7 (GND), U5.9 (GND2), U6.2 (GND), U7.9 (GND2), U7.15 (GND2), U8.5 (GND), U9.12 (Vss), U10.3 (DGND), U10.4 (AGND), U10.13 (DGND), U11.6 (REF), U14.6 (REF), U16.10 (S4B), U16.15 (GND), U18.10 (S4B), U18.15 (GND), U19.3 (GND), U20.3 (GND)
IOUT0: R3.2, U11.1 (-IN), U18.8 (DA)
IOUT1: R6.2, U14.1 (-IN), U16.8 (DA)
ISENSE0: U11.7 (OUT), U19.8
ISENSE1: U14.7 (OUT), U20.8
MISO: U1.14 (12_MISO0), U7.6 (OUTD)
MISOi: U7.11 (IND), U10.12 (DOUT)
MOSI: U1.13 (11_MOSI0), U7.3 (INA)
MOSIi: U7.14 (OUTA), U9.5 (SDI), U10.2 (DIN)
NLDAC: U1.11 (9_PWM_RX2_CS0), U7.5 (INC)
NLDACi: U7.12 (OUTC), U9.8 (~LDAC)
unnamed: C42.1, U10.5 (REFIN/OUT)
unnamed: J1.1 (In), J3.1, U1.49 (22_A8_PWM_Touch)
unnamed: J5.1 (In), J7.1, U1.50 (23_A9_PWM_Touch)
unnamed: R1.1, U12.3 (+)
unnamed: R2.1, U13.3 (+)
unnamed: R3.1, R5.1, U11.4 (+IN), U12.1 (REF)
unnamed: R4.1, R6.1, U13.1 (REF), U14.4 (+IN)
unnamed: R4.2, U13.5 (SENSE), U13.6
unnamed: R5.2, U12.5 (SENSE), U12.6
unnamed: R7.1, U11.3 (RG2)
unnamed: R7.2, U11.2 (RG)
unnamed: R8.1, U14.3 (RG2)
unnamed: R8.2, U14.2 (RG)
unnamed: R9.2, U16.4 (S1A), U16.7 (S4A)
unnamed: R10.1, R11.2, R15.1
unnamed: R12.1, R14.2, R16.1
unnamed: R13.1, U18.4 (S1A), U18.7 (S4A)
unnamed: R15.2, R17.1, U15.2 (-)
unnamed: R16.2, R18.1, U17.2 (-)
unnamed: U10.7 (VIN0), U19.1
unnamed: U10.8 (VIN1), U20.1
unnamed: U16.6 (S3A), U16.11 (S3B)
unnamed: U16.5 (S2A), U16.12 (S2B)
unnamed: U18.6 (S3A), U18.11 (S3B)
unnamed: U18.5 (S2A), U18.12 (S2B)
OE0: U1.8 (6_PWM), U5.4 (INC)
OE0i: U5.13 (OUTC), U18.1 (A0)
OE1: U1.7 (5_PWM_tx1_miso1), U5.5 (IND)
OE1i: U5.12 (OUTD), U18.16 (A1), U19.6
OE2: U1.6 (4_PWM_CAN0RX_SDA2), U5.6 (INE)
OE2i: U5.11 (OUTE), U16.1 (A0)
OE3: U1.5 (3_PWM_CAN0TX_SCL2), U5.7 (INF)
OE3i: U5.10 (OUTF), U16.16 (A1), U20.6
OUT0: J9.1, J10.1 (In), U18.9 (DB), U19.2
OUT1: J11.1, J12.1 (In), U16.9 (DB), U20.2
SCK0: U1.40 (13_SCK0_LED), U7.4 (INB)
SCK0i: U7.13 (OUTB), U9.4 (SCK), U10.14 (SCLK)
VOUT0: R17.2, U15.6, U18.13 (S1B)
VOUT1: R18.2, U16.13 (S1B), U17.6
VUSB: C1.2, U1.53 (Vin), U2.1 (+Vin)

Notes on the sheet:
gain is Rsense*(1+49.4k/Rg) = 250*(1+49.4k/1.2k) = 10.5 mV/uA Voltage output range is thus +-833*0.0105 = +-8.7V output needs to be within +-10V
Max current output (0ohm load) is 2.5V/3k = +- 833uA. Current resolution is 5V/4096/3k = 0.4uA Max voltage output (infinite load) is 40/43*12V = 11.16V
OE0 OE1 Output Input (ADC) 0 0 VOLTAGE OUT0 1 0 CURRENT OUT0 0 1 CURRENT ISENSE0 1 1 GND ISENSE0
